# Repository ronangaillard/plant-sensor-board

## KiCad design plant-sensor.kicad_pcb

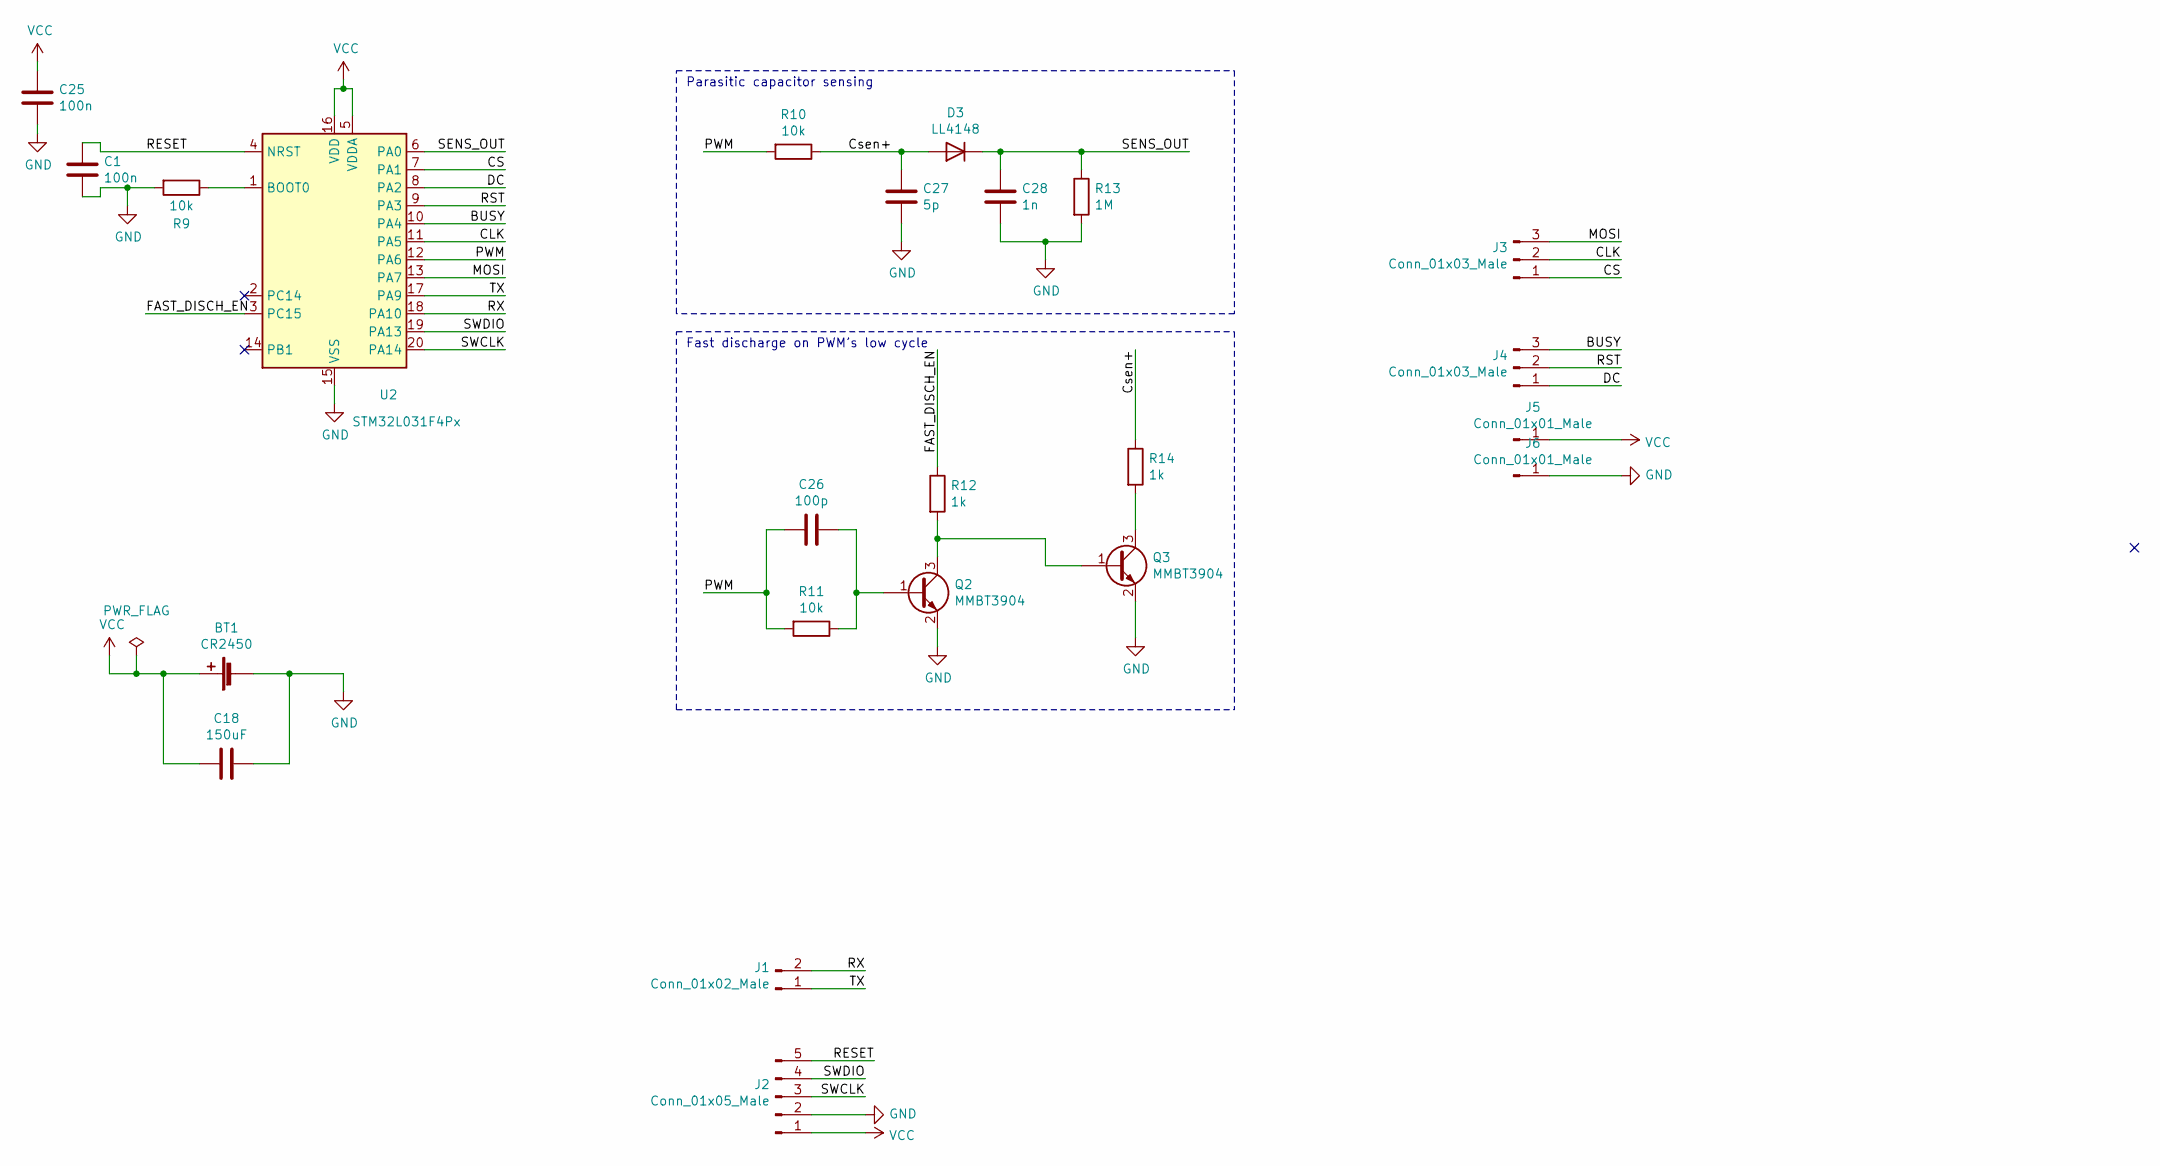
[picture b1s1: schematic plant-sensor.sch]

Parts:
BT1: CR2450; BatteryHolder_Keystone_3002_1x2032
C1, C25: 100n; C_0603_1608Metric_Pad1.05x0.95mm_HandSolder
C18: 150uF; C_1206_3216Metric_Pad1.42x1.75mm_HandSolder
C26: 100p; C_0603_1608Metric_Pad1.05x0.95mm_HandSolder
C27: 5p; C_0603_1608Metric_Pad1.05x0.95mm_HandSolder
C28: 1n; C_0603_1608Metric_Pad1.05x0.95mm_HandSolder
D3: LL4148; D_MiniMELF
J1: Conn_01x02_Male; PinHeader_1x02_P2.54mm_Vertical
J2: Conn_01x05_Male; PinHeader_1x05_P2.54mm_Vertical
J3, J4: Conn_01x03_Male; PinHeader_1x03_P2.54mm_Vertical
J5, J6: Conn_01x01_Male; PinHeader_1x01_P2.54mm_Vertical
Q2, Q3: MMBT3904; SOT-23
R9, R10, R11: 10k; R_0603_1608Metric_Pad1.05x0.95mm_HandSolder
R12, R14: 1k; R_0603_1608Metric_Pad1.05x0.95mm_HandSolder
R13: 1M; R_0603_1608Metric_Pad1.05x0.95mm_HandSolder
U2: STM32L031F4Px; TSSOP-20_4.4x6.5mm_P0.65mm

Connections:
/BUSY: J4.3, U2.10 (PA4)
/CLK: J3.2, U2.11 (PA5)
/CS: J3.1, U2.7 (PA1)
/Csen+: C27.1, D3.2 (A), R10.1, R14.1
/DC: J4.1, U2.8 (PA2)
/FAST_DISCH_EN: R12.1, U2.3 (PC15)
/MOSI: J3.3, U2.13 (PA7)
/PWM: C26.2, R10.2, R11.2, U2.12 (PA6)
/RESET: C1.1, J2.5, U2.4 (NRST)
/RST: J4.2, U2.9 (PA3)
/RX: J1.2, U2.18 (PA10)
/SENS_OUT: C28.1, D3.1 (K), R13.1, U2.6 (PA0)
/SWCLK: J2.3, U2.20 (PA14)
/SWDIO: J2.4, U2.19 (PA13)
/TX: J1.1, U2.17 (PA9)
GND: BT1.2 (-), C1.2, C18.1, C25.2, C27.2, C28.2, J2.2, J6.1, Q2.2 (E), Q3.2 (E), R9.2, R13.2, U2.15 (VSS)
unnamed: C26.1, Q2.1 (B), R11.1
unnamed: Q2.3 (C), Q3.1 (B), R12.2
unnamed: Q3.3 (C), R14.2
unnamed: R9.1, U2.1 (BOOT0)
VCC: BT1.1 (+), C18.2, C25.1, J2.1, J5.1, U2.5 (VDDA), U2.16 (VDD)

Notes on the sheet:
Parasitic capacitor sensing
Fast discharge on PWM’s low cycle

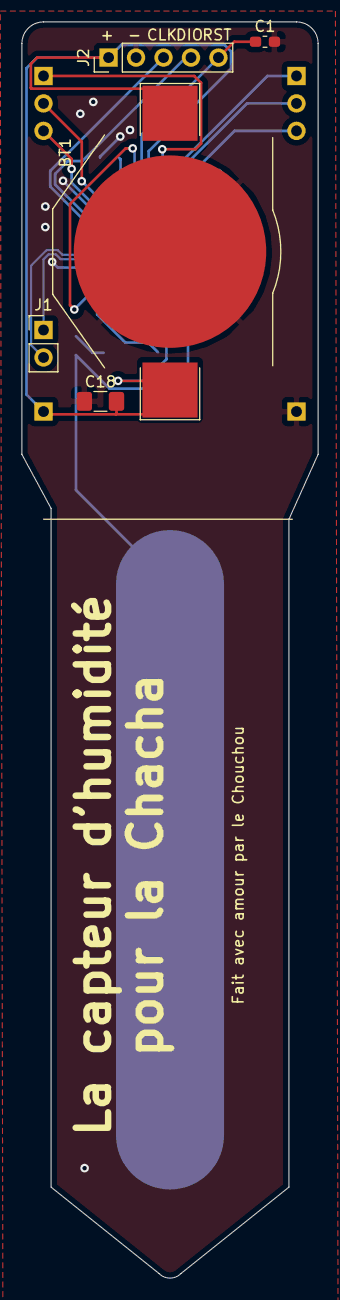
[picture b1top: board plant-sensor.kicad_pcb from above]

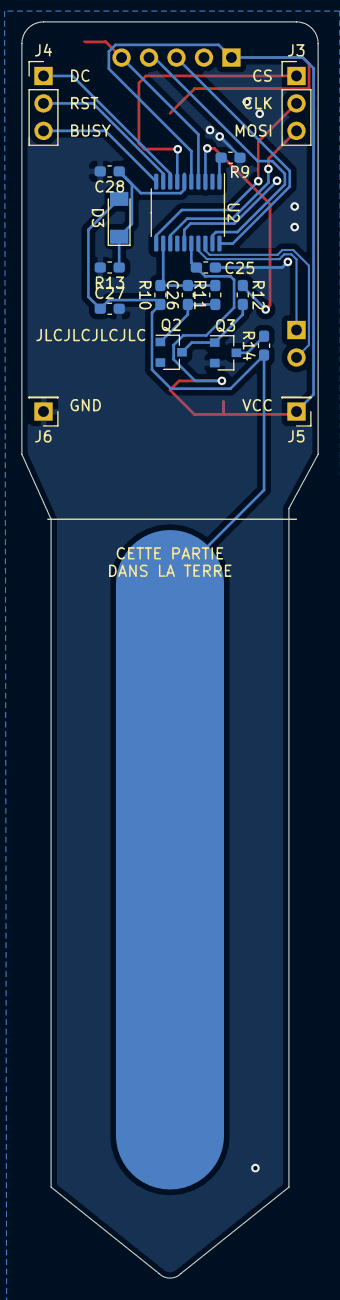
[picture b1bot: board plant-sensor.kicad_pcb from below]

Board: 2 copper layers, 27.4 x 116.2 mm, 23 parts (18 on the bottom side), 21 nets.

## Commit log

2021-08-14 version sent to jlc
